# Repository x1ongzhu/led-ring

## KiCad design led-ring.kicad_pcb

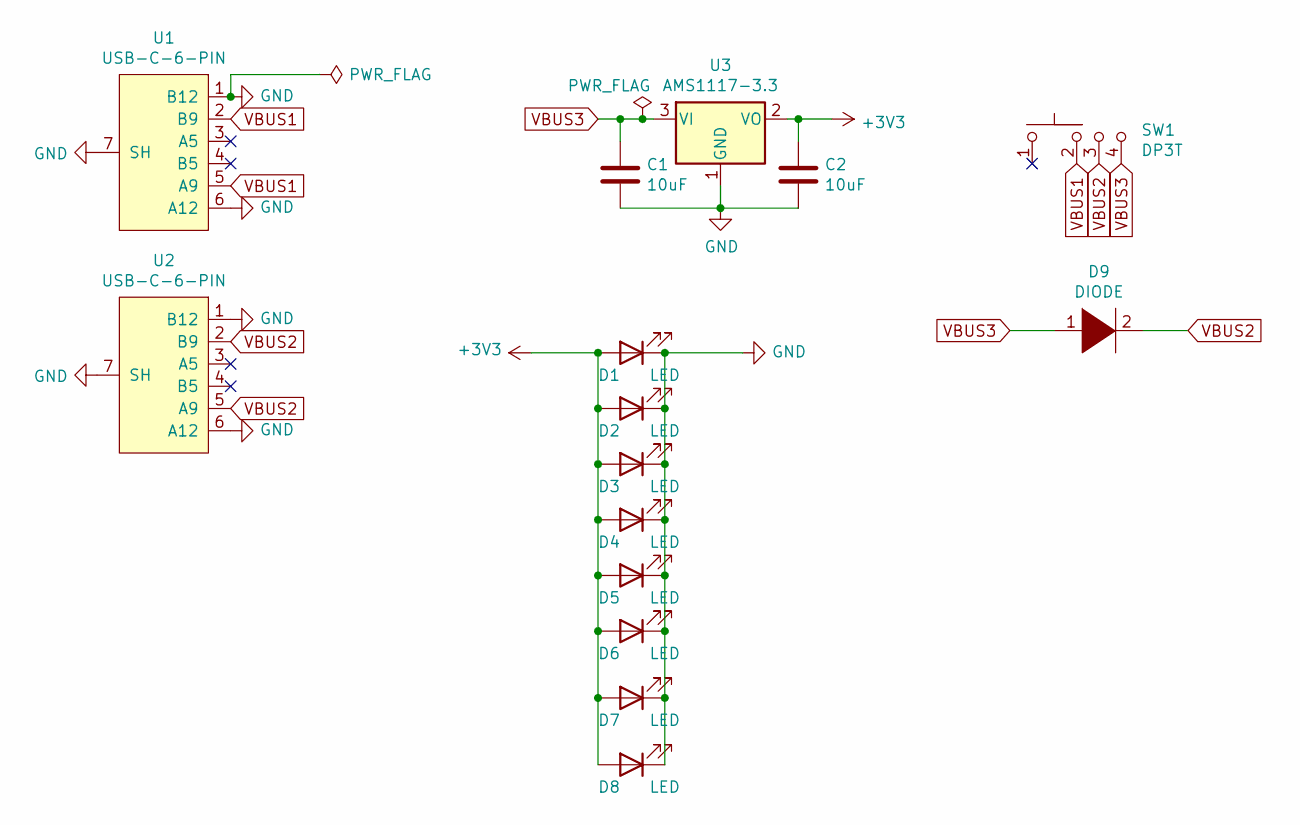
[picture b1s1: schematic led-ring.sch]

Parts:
C1, C2: 10uF; C_0402_1005Metric
D1, D2, D3, D4, D5, D6, D7, D8: LED; LED_PLCC_2835
D9: DIODE; D_SMA
SW1: DP3T; SS-1400S-L1
U1, U2: USB-C-6-PIN; TYPE-C-31-D-01
U3: AMS1117-3.3; SOT-89-3

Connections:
+3V3: C2.1, D1.2 (A), D2.2 (A), D3.2 (A), D4.2 (A), D5.2 (A), D6.2 (A), D7.2 (A), D8.2 (A), U3.2 (VO)
GND: C1.2, C2.2, D1.1 (K), D2.1 (K), D3.1 (K), D4.1 (K), D5.1 (K), D6.1 (K), D7.1 (K), D8.1 (K), U1.1 (B12), U1.6 (A12), U1.7 (SH), U2.1 (B12), U2.6 (A12), U2.7 (SH), U3.1 (GND)
VBUS1: SW1.2, U1.2 (B9), U1.5 (A9)
VBUS2: D9.2 (A), SW1.3, U2.2 (B9), U2.5 (A9)
VBUS3: C1.1, D9.1 (K), SW1.4, U3.3 (VI)

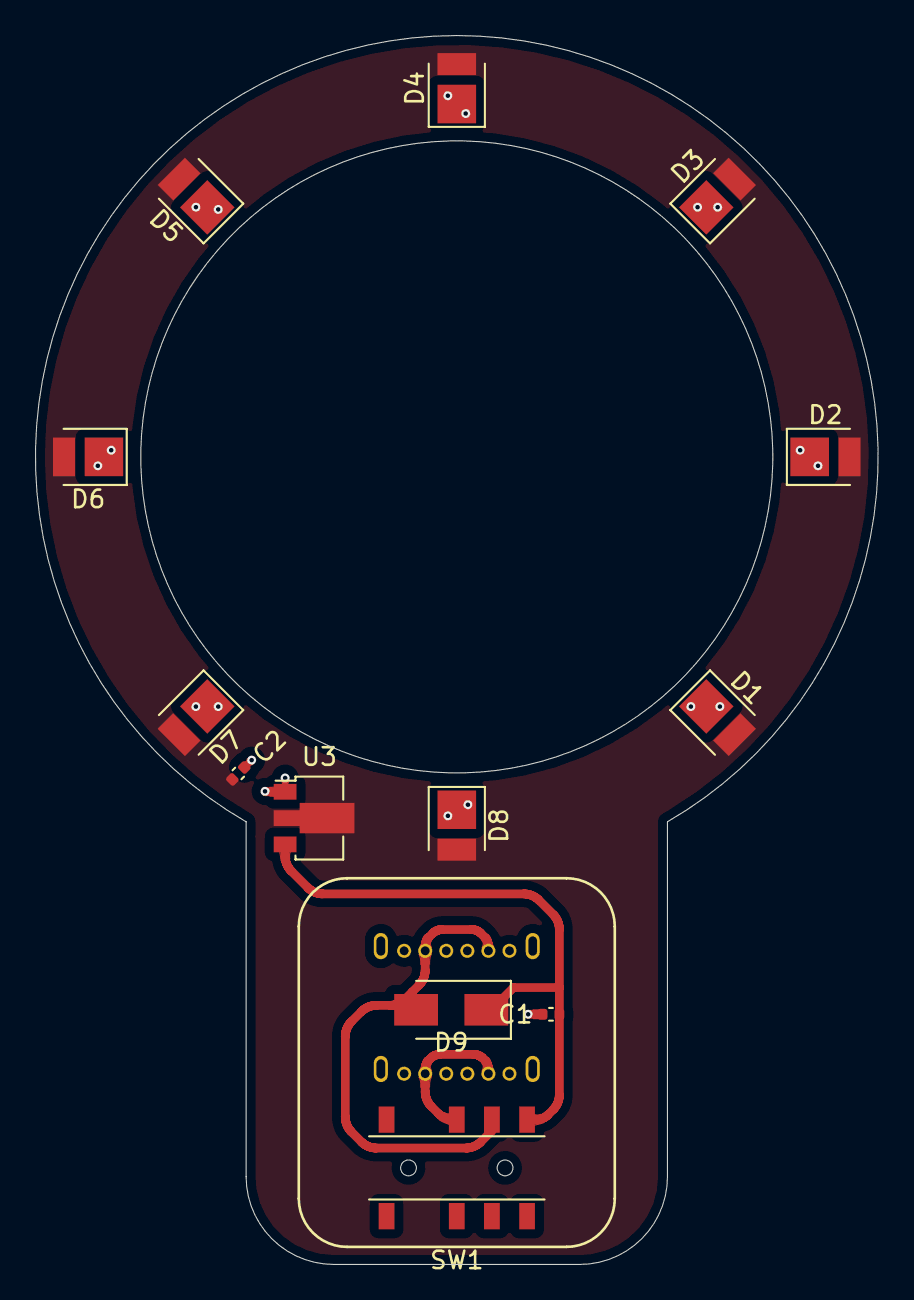
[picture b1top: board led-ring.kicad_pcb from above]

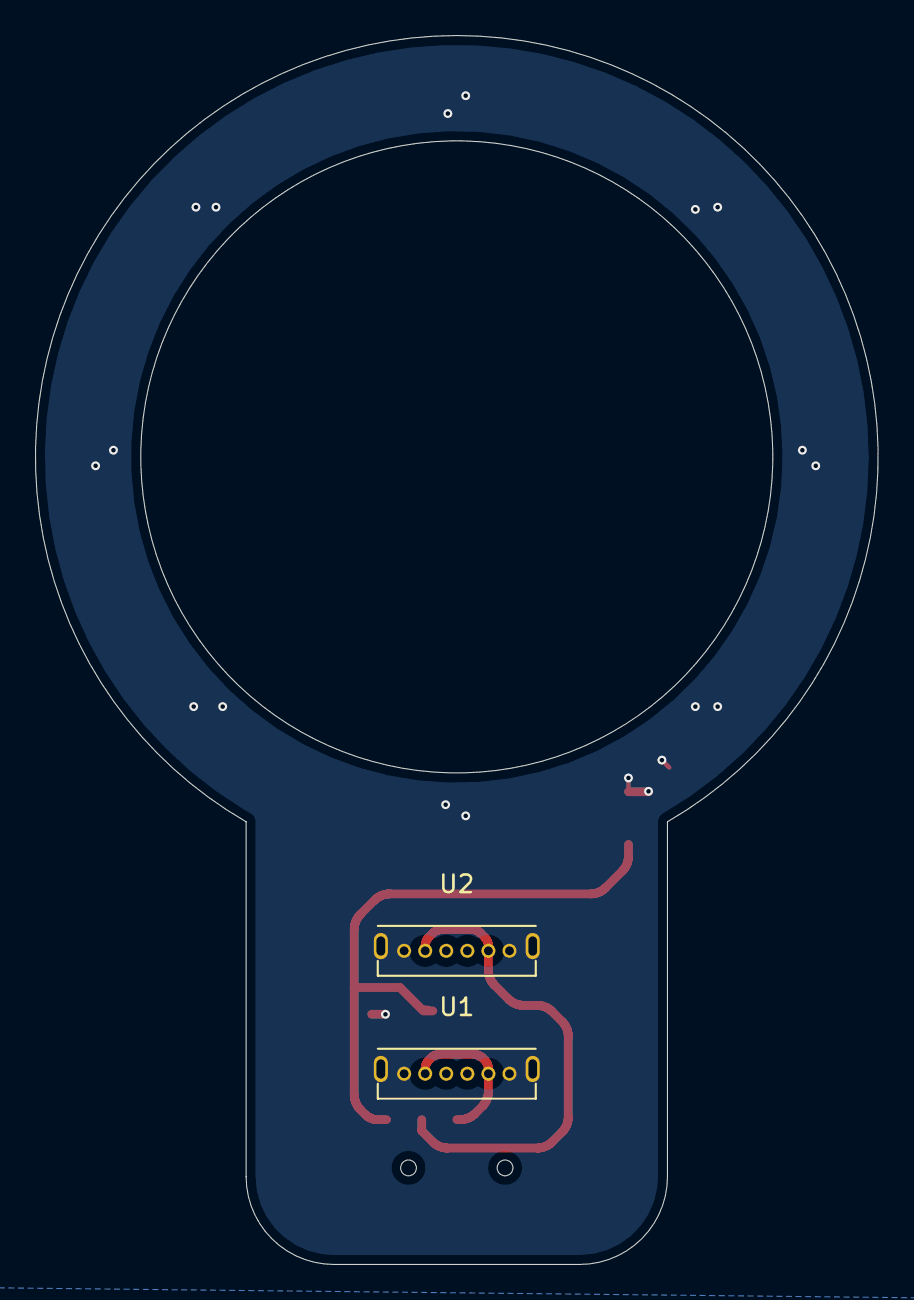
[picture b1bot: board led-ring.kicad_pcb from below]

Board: 2 copper layers, 48.0 x 70.0 mm, 15 parts (2 on the bottom side), 5 nets.
